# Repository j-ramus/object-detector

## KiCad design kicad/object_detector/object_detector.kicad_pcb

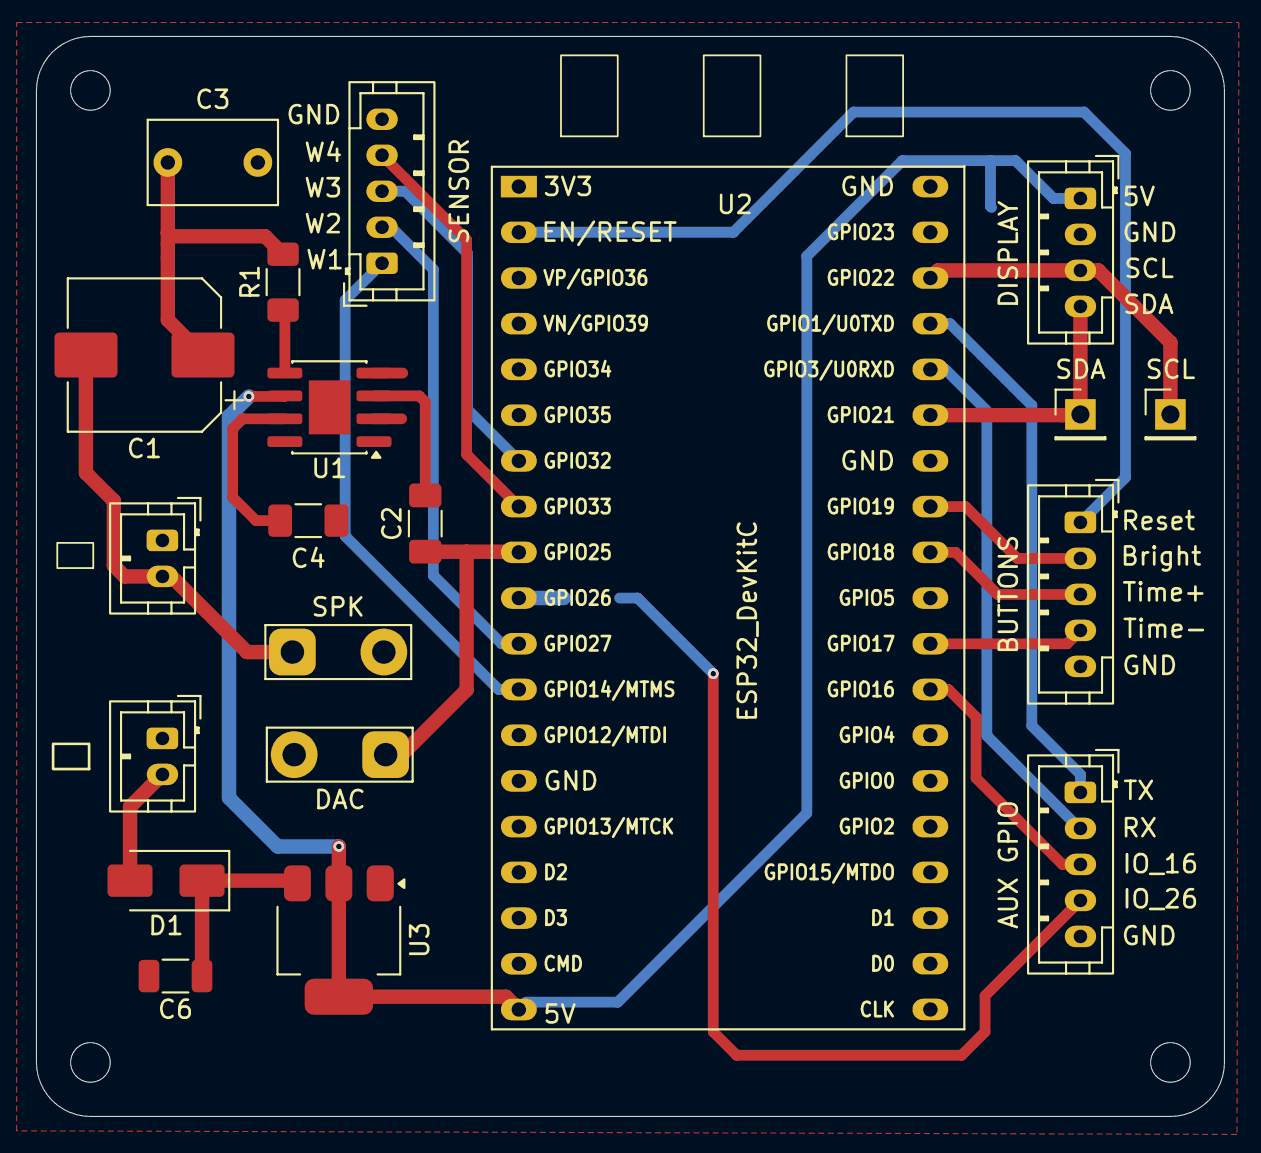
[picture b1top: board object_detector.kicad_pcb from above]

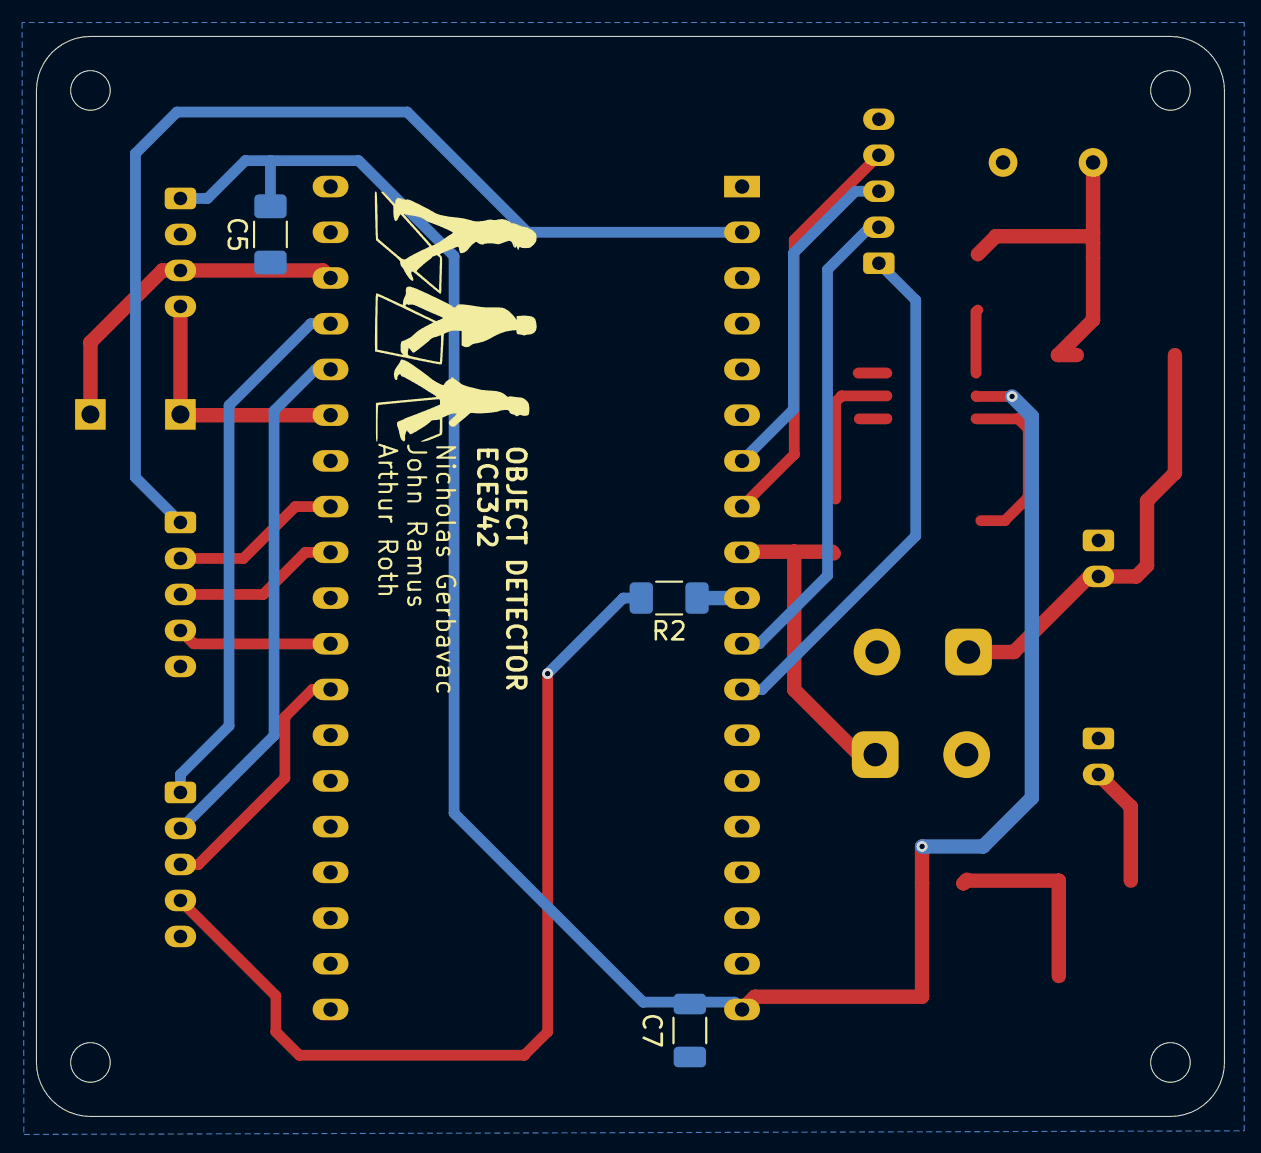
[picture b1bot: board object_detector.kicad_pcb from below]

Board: 2 copper layers, 66.0 x 60.0 mm, 27 parts (3 on the bottom side), 25 nets.

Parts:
AUX GPIO: Conn_01x05; JST_PH_B5B-PH-K_1x05_P2.00mm_Vertical
BUTTONS: Conn_01x05; JST_PH_B5B-PH-K_1x05_P2.00mm_Vertical
C1: 220u; CP_Elec_8x10
C2, C5: 100n; C_1206_3216Metric_Pad1.33x1.80mm_HandSolder
C3: 1u; C_Rect_L7.0mm_W4.5mm_P5.00mm
C4: 47n; C_1206_3216Metric_Pad1.33x1.80mm_HandSolder
C6, C7: 10uF; C_1206_3216Metric
D1: B220; D_SMA
DAC: DAC_signal; TestPoint_2Pads_Pitch5.08mm_Drill1.3mm
DISPLAY: Conn_01x04; JST_PH_B4B-PH-K_1x04_P2.00mm_Vertical
H1, H2, H3, H4: MountingHole; MountingHole_2.2mm_M2
R1: 100R; R_1206_3216Metric_Pad1.30x1.75mm_HandSolder
R2: 0R; R_1206_3216Metric_Pad1.30x1.75mm_HandSolder
SCL: SCL; PinHeader_1x01_P2.54mm_Vertical
SDA: SDA; PinHeader_1x01_P2.54mm_Vertical
SENSOR: Conn_01x05; JST_PH_B5B-PH-K_1x05_P2.00mm_Vertical
SPK: Spk_signal; TestPoint_2Pads_Pitch5.08mm_Drill1.3mm
Speaker: Conn_01x02; JST_PH_B2B-PH-K_1x02_P2.00mm_Vertical
U1: LM386; SOIC-8-1EP_3.9x4.9mm_P1.27mm_EP2.29x3mm
U2: ESP32_DevKitC; ESP32-DevKitC
U3: NCP1117-5.0_SOT223; SOT-223-3_TabPin2
󰂅: Conn_01x02; JST_PH_B2B-PH-K_1x02_P2.00mm_Vertical

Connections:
5V: C5.2, C7.1, DISPLAY.1, U1.6 (V+), U2.19 (5V_in), U3.2 (VO)
BRIGHTNESS: BUTTONS.2, U2.31 (IO_19)
DAC: C2.1, DAC.1, U2.9 (IO_25)
EXT_DAC: R2.1, U2.10 (IO_26)
GND: AUX GPIO.5, BUTTONS.5, C3.2, C4.1, C5.1, C6.2, C7.2, DISPLAY.2, SENSOR.5, Speaker.1, U1.2 (-), U1.4 (GND), U2.14 (GND), U2.32 (GND), U2.38 (GND), U3.1 (GND), 󰂅.1
GPIO_16: AUX GPIO.3, U2.27 (IO_16)
unnamed: AUX GPIO.4, R2.2
unnamed: C1.1, C3.1, R1.2
unnamed: D1.2 (A), 󰂅.2
unnamed: C6.1, D1.1 (K), U3.3 (VI)
unnamed: R1.1, U1.5
unnamed: C1.2, SPK.1, Speaker.2
unnamed: C2.2, U1.3 (+)
unnamed: C4.2, U1.7 (BYPASS)
RESET: BUTTONS.1, U2.2 (EN)
RX: AUX GPIO.2, U2.34 (RX)
SCL: DISPLAY.3, SCL.1, U2.36 (IO_22)
SDA: DISPLAY.4, SDA.1, U2.33 (IO_21)
TIME_DEC: BUTTONS.4, U2.28 (IO_17)
TIME_INC: BUTTONS.3, U2.30 (IO_18)
TX: AUX GPIO.1, U2.35 (TX)
WEIGH_1: SENSOR.1, U2.12 (IO_14)
WEIGH_2: SENSOR.2, U2.11 (IO_27)
WEIGH_3: SENSOR.3, U2.7 (IO_32)
WEIGH_4: SENSOR.4, U2.8 (IO_33)

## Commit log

2026-01-30 alarm working
2026-02-18 about to start on display
2026-02-19 put my sutff on kicad schematic
2026-02-23 kicad layout for ramus stuff
2026-02-26 updated PCB schematic
2026-02-26 added backup zip of old schematic
2026-02-26 changed LDO connector input
2026-02-26 preliminary layout
2026-02-26 added dimensions to PCB footprint
2026-02-26 adding MC main code and test scripts
2026-02-28 PCB edits, MC code edits
2026-02-28 board revision friday
2026-03-04 final stuff on the pcb that i forgot to commit
2026-03-04 made alarm.h and removed test code frm alarm.c
2026-03-04 Remove build directories and add .gitignore
    Untrack all build/ output directories from MC, display, and alarm
    subdirectories (5806 files). Add root .gitignore to prevent build
    artifacts from being committed in the future.
2026-03-04 Remove .DS_Store files and add to .gitignore
    Untrack all macOS .DS_Store metadata files and update .gitignore to
    prevent them from being committed. Also deleted alarm and display build
    directories from disk.
2026-03-05 display changed to be called from MC
2026-03-05 fixed ssd1306
2026-03-05 interagted alarm.c and display.c into MC.c
2026-03-10 added timer callback and changed pins
2026-03-10 added some of the timer functionality to MC
2026-03-11 added countdown to main code
